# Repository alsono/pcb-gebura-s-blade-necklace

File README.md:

i'm rewriting this because github genuinely vaporized my last one  (i'm sick this is the best writing i can manage i swear i'll rewrite all of this) <br>
# intro 
just a pcb with togglable lights (via button) that uses a 555 timer and like vibrates <br>
heres the circuit <br>
<br>
and heres the pcb <br>
<br>
and a 3d render of it <br>
<br>
heres what it looks like when in jlc pcb in both red and black <br>
 <br>
 <br>
bill of materials for what you'll need (all comes in the solder kit from the hack club event [solder](https://solder.hackclub.com/))
|Reference     |Qty|Value       |DNP|Exclude from BOM|Exclude from Board|Footprint                                                  |Datasheet                                                                 |
|--------------|---|------------|---|----------------|------------------|-----------------------------------------------------------|--------------------------------------------------------------------------|
|BT1,BT2       |2  |Battery_Cell|   |                |                  |Battery:BatteryHolder_Keystone_3034_1x20mm                 |                                                                          |
|C1            |1  |C           |   |                |                  |Capacitor_THT:CP_Axial_L10.0mm_D4.5mm_P15.00mm_Horizontal  |                                                                          |
|D1,D2,D3,D4,D5|5  |LED         |   |                |                  |LED_THT:LED_D5.0mm_Horizontal_O1.27mm_Z3.0mm               |                                                                          |
|M1            |1  |Motor_DC    |   |                |                  |Resistor_THT:R_Axial_DIN0207_L6.3mm_D2.5mm_P2.54mm_Vertical|                                                                          |
|Q1            |1  |2N3904      |   |                |                  |Package_TO_SOT_THT:TO-92_Inline                            |https://www.onsemi.com/pub/Collateral/2N3903-D.PDF                        |
|R1,R2,R4      |3  |4.7k        |   |                |                  |Resistor_THT:R_Axial_DIN0207_L6.3mm_D2.5mm_P2.54mm_Vertical|                                                                          |
|R3            |1  |47k         |   |                |                  |Resistor_THT:R_Axial_DIN0207_L6.3mm_D2.5mm_P2.54mm_Vertical|                                                                          |
|SW2           |1  |SW_Push     |   |                |                  |Button_Switch_THT:KSA_Tactile_SPST                         |                                                                          |
|U2            |1  |ICM7555xP   |   |                |                  |Package_DIP:DIP-8_W7.62mm                                  |http://www.intersil.com/content/dam/Intersil/documents/icm7/icm7555-56.pdf|
### my slack id is U0A5NF4LR8U

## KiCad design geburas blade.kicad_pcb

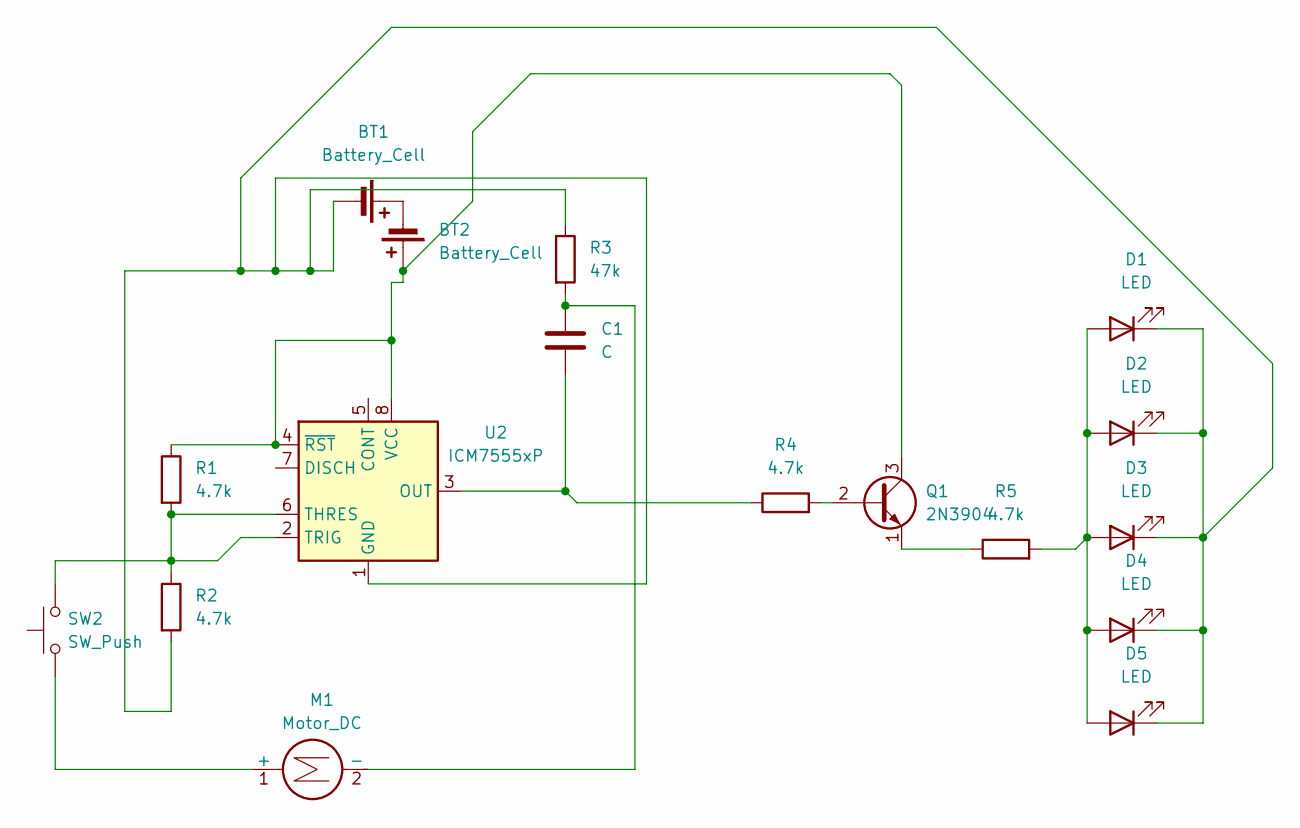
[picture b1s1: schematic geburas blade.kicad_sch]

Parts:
BT1, BT2: Battery_Cell; BatteryHolder_Keystone_3034_1x20mm
C1: C; CP_Axial_L10.0mm_D4.5mm_P15.00mm_Horizontal
D1, D2, D3, D4, D5: LED; LED_D5.0mm_Horizontal_O1.27mm_Z3.0mm
M1: Motor_DC; R_Axial_DIN0207_L6.3mm_D2.5mm_P2.54mm_Vertical
Q1: 2N3904; TO-92_Inline
R1, R2, R4, R5: 4.7k; R_Axial_DIN0207_L6.3mm_D2.5mm_P2.54mm_Vertical
R3: 47k; R_Axial_DIN0207_L6.3mm_D2.5mm_P2.54mm_Vertical
SW2: SW_Push; KSA_Tactile_SPST
U2: ICM7555xP; DIP-8_W7.62mm

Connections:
unnamed: BT1.1 (+), BT2.2 (-)
unnamed: BT1.2 (-), D1.1 (K), D2.1 (K), D3.1 (K), D4.1 (K), D5.1 (K), R2.2, R3.1, U2.1 (GND)
unnamed: BT2.1 (+), Q1.3 (C), R1.1, U2.4 (~RST), U2.8 (VCC)
unnamed: D1.2 (A), D2.2 (A), D3.2 (A), D4.2 (A), D5.2 (A), R5.2
unnamed: M1.1 (+), SW2.1
unnamed: C1.1, M1.2 (-), R3.2
unnamed: Q1.2 (B), R4.2
unnamed: Q1.1 (E), R5.1
unnamed: C1.2, R4.1, U2.3 (OUT)
unnamed: R1.2, R2.1, SW2.2, U2.2 (TRIG), U2.6 (THRES)

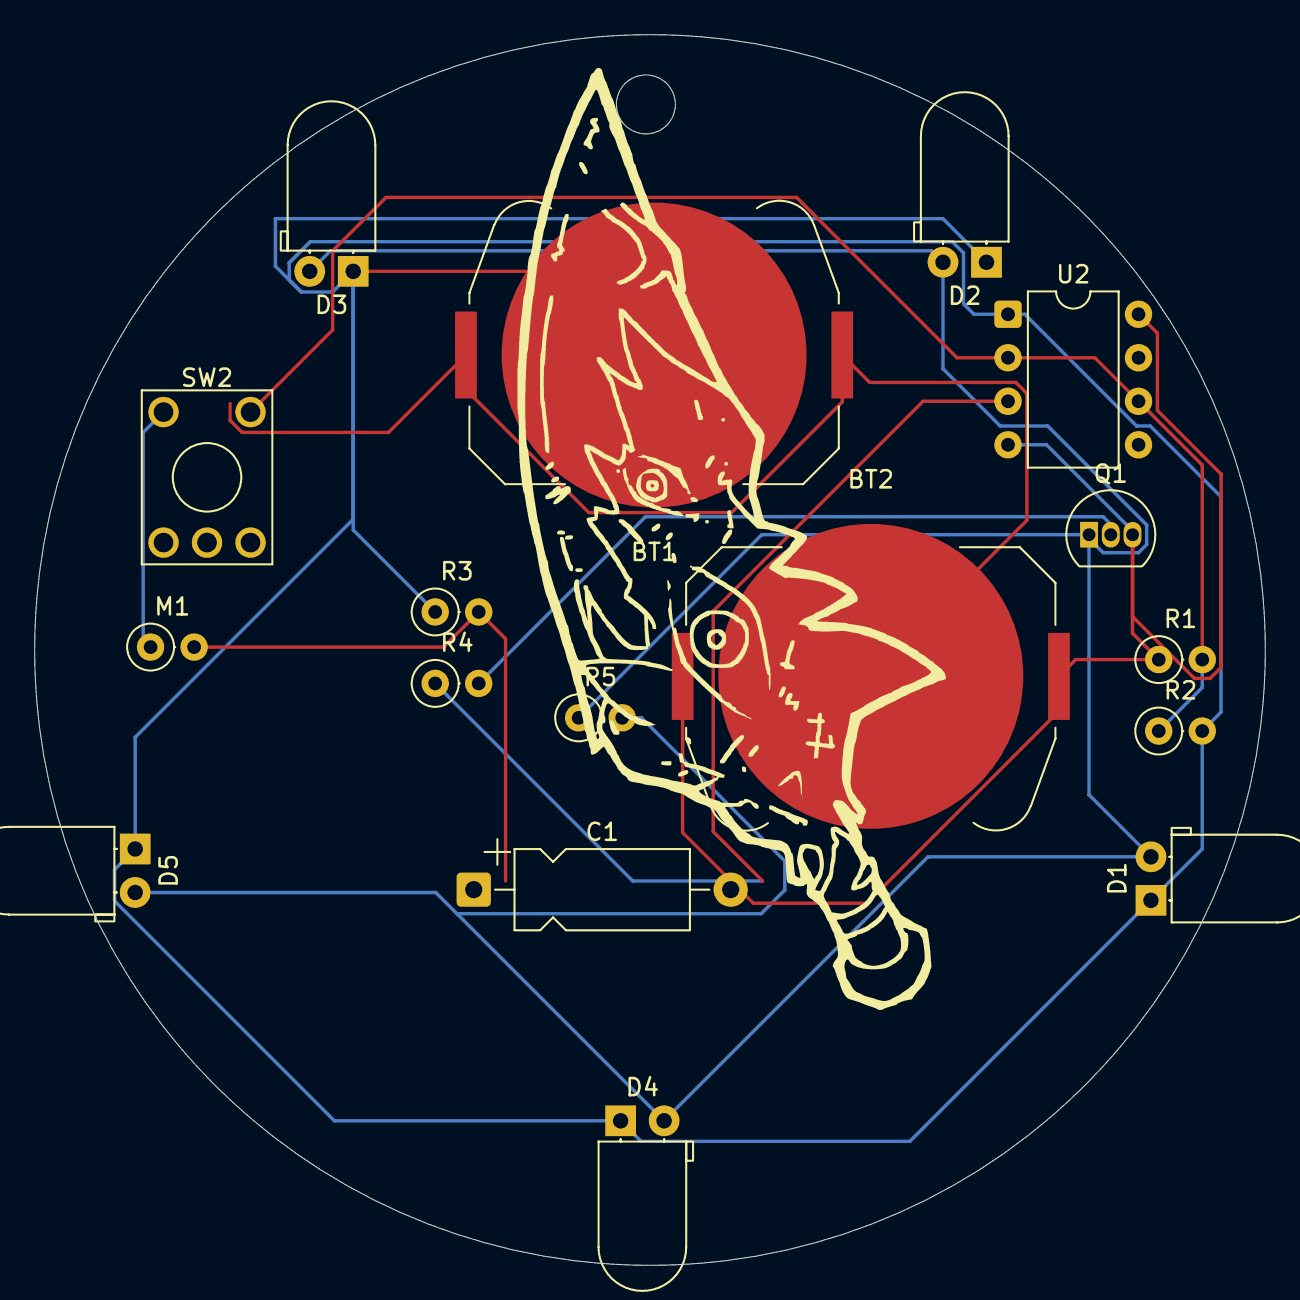
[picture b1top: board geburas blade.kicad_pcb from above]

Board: 2 copper layers, 71.8 x 71.8 mm, 17 parts (0 on the bottom side), 10 nets.
